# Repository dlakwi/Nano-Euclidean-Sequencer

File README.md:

# Nano-Euclidean-Sequencer
Build of KeLaiFu's Nano-Euclidean-Sequencer.
Illuminated pushbuttons and toggle switch are different.

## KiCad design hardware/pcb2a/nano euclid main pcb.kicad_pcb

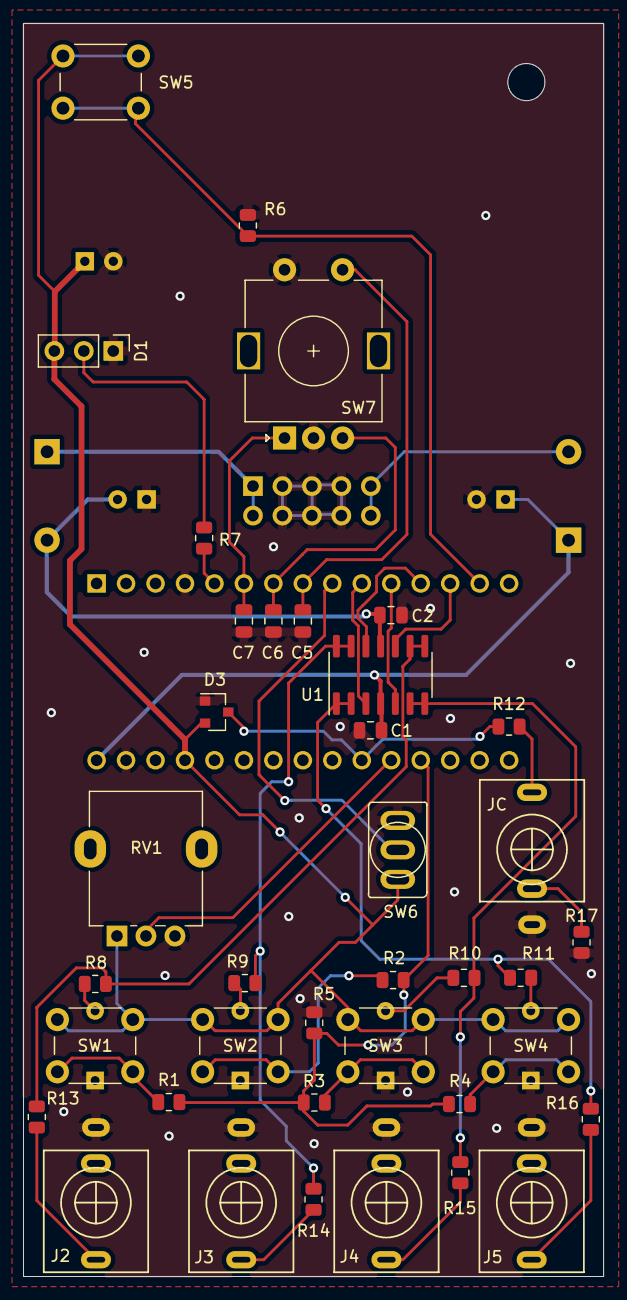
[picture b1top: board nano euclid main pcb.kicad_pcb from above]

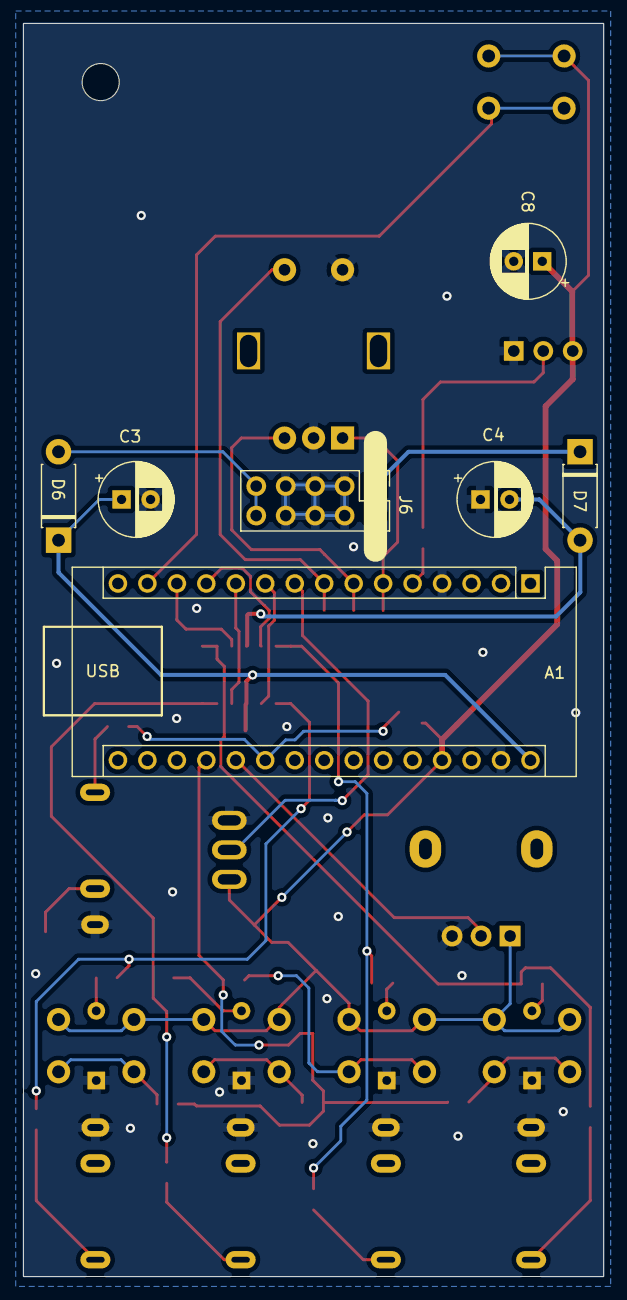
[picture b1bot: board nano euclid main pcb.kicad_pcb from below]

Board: 2 copper layers, 50.0 x 108.0 mm, 45 parts (7 on the bottom side), 38 nets.

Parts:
A1: Arduino_Nano_v3.x; Arduino_Nano
C1, C2: 100n; C_0805_2012Metric
C3, C4: 10u; CP_Radial_D6.3mm_P2.50mm
C5, C6, C7: 10n; C_0805_2012Metric
C8: 47u; CP_Radial_D6.3mm_P2.50mm
D1: NeoPixel_THT; PinHeader_1x03_P2.54mm_Vertical
D3: BAT54S; SOT-23
D6, D7: 1N5817; D_DO-41_SOD81_P7.62mm_Horizontal
J2, J3, J4, J5: AudioJack2_Ground; PJ398SM
J6: Synth_power_2x5; PinHeader_2x05_P2.54mm_Vertical
JC: CLOCK; PJ398SM
R1, R12, R13, R14, R15, R16: 1k; R_0805_2012Metric
R2: 2k2; R_0805_2012Metric
R3, R6, R17: 4k7; R_0805_2012Metric
R4, R5: 10k; R_0805_2012Metric
R7: 220R; R_0805_2012Metric
R8, R9, R10, R11: Rled; R_0805_2012Metric
RV1: R_Potentiometer; Potentiometer_Alpha_RD901F-40-00D_Single_Vertical
SW1, SW2, SW3, SW4: SW_Push; SW_PUSH_LED_6mm
SW5: SW_Push; SW_PUSH_6mm
SW6: Toggle_SPDT_SubMini_2pos; Switch_Toggle_SPDT_SubMini
SW7: RotaryEncoder_Switch; RotaryEncoder_Alps_EC11E-Switch_Vertical_H20mm
U1: TL074; SOIC-14_3.9x8.7mm_P1.27mm

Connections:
+12V: A1.30 (VIN), C1.1, C3.1, D6.1 (K), U1.4 (V+)
-12V: C2.1, C4.2, D7.2 (A), U1.11 (V-)
Ch1-out: R8.1, R13.2, U1.8, U1.9 (-)
Ch2-out: R9.2, R14.2, U1.13 (-), U1.14
Ch3-out: R10.2, R15.2, U1.6 (-), U1.7
Ch4-out: R11.2, R16.2, U1.1, U1.2 (-)
GND: A1.4 (GND), A1.29 (GND), C1.2, C2.2, C3.2, C4.1, C5.2, C6.2, C7.2, C8.2, D1.1 (DOUT), D3.1, J2.S, J3.S, J4.S, J5.S, J6.3 (GND), J6.4 (GND), J6.5 (GND), J6.6 (GND), J6.7 (GND), J6.8 (GND), JC.S, R5.2, R6.1, R17.1, RV1.3, SW1.4 (K), SW2.4 (K), SW3.4 (K), SW4.4 (K), SW6.1, SW7.C, SW7.S2
JC-TN: JC.TN, R17.2
unnamed: A1.5 (D2), R7.2
unnamed: A1.6 (D3), C7.1, SW7.A
unnamed: A1.7 (D4), C6.1, SW7.B
unnamed: A1.8 (D5), C5.1, SW7.S1
unnamed: A1.9 (D6), SW6.2
unnamed: A1.10 (D7), U1.3 (+)
unnamed: A1.11 (D8), U1.5 (+)
unnamed: A1.12 (D9), U1.12 (+)
unnamed: A1.13 (D10), U1.10 (+)
unnamed: A1.14 (D11), R6.2, SW5.2
unnamed: A1.19 (A0), R1.1, R2.1, R3.1, R4.1, R5.1
unnamed: A1.20 (A1), RV1.2
unnamed: A1.21 (A2), D3.3, R12.2
unnamed: A1.27 (+5V), C8.1, D1.3 (VDD), D3.2, RV1.1, SW1.1, SW2.1, SW3.1, SW4.1, SW5.1, SW6.3
unnamed: D1.2 (GND), R7.1
unnamed: D6.2 (A), J6.9 (+12V), J6.10 (+12V)
unnamed: D7.1 (K), J6.1 (-12V), J6.2 (-12V)
unnamed: J2.T, R13.1
unnamed: J3.T, R14.1
unnamed: J4.T, R15.1
unnamed: J5.T, R16.1
unnamed: JC.T, R12.1
unnamed: R1.2, SW1.2
unnamed: R2.2, SW2.2
unnamed: R3.2, SW3.2
unnamed: R4.2, SW4.2
unnamed: R8.2, SW1.3 (A)
unnamed: R10.1, SW3.3 (A)
unnamed: R11.1, SW4.3 (A)
unnamed: R9.1, SW2.3 (A)
